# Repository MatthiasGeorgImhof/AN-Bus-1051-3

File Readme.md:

CAN transceiver from TX and RX to HIGH and LOW
Inspired by Adafruit but without buckconverter. Provide both 5 and 3.3V on pins

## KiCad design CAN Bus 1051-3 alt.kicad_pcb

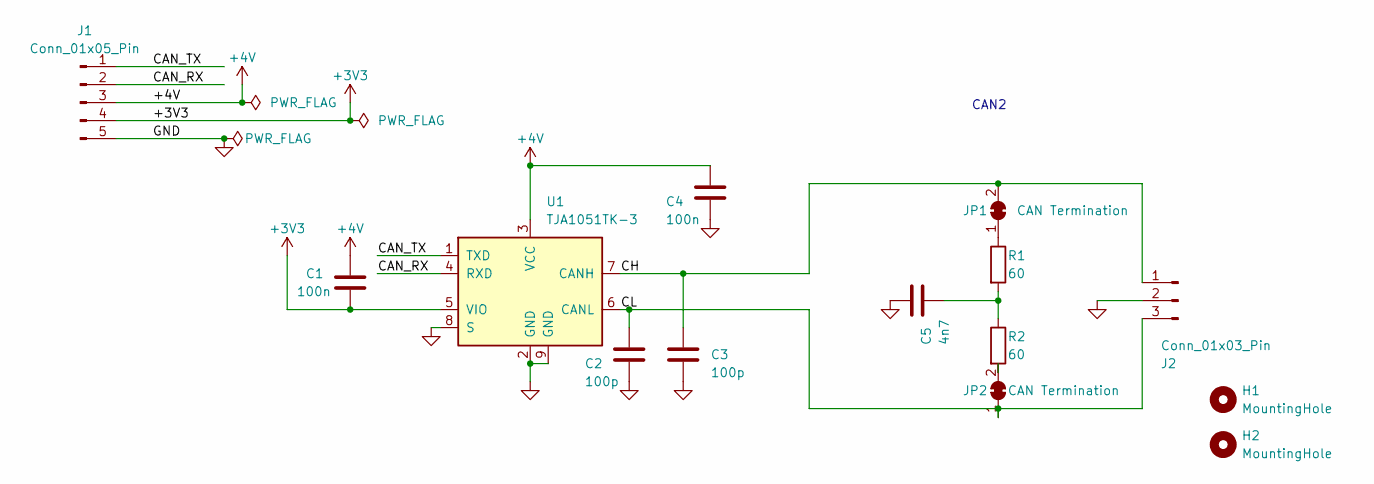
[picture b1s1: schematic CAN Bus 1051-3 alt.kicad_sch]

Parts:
C1, C4: 100n; C_0402_1005Metric; Voltage 16; Part Number CC0402KRX7R7BB104
C2, C3: 100p; C_0402_1005Metric; Voltage 16; Part Number CC0402KRX7R7BB101
C5: 4n7; C_0402_1005Metric; Voltage 16; Part Number CC0402KRX7R8BB472
H1, H2: MountingHole; MountingHole_2.2mm_M2
J1: Conn_01x05_Pin; PinHeader_1x05_P2.54mm_Vertical
J2: Conn_01x03_Pin; PinHeader_1x03_P2.54mm_Vertical
JP1, JP2: CAN Termination; SolderJumper-2_P1.3mm_Bridged_Pad1.0x1.5mm
R1, R2: 60; R_0402_1005Metric; Part Number RC0402FR-0760R4L
U1: TJA1051TK-3; DFN-8-1EP_3x3mm_P0.65mm_EP1.55x2.4mm; Part Number TJA1051TK/3,118

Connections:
+3V3: C1.2, J1.4, U1.5 (VIO)
+4V: C1.1, C4.1, J1.3, U1.3 (VCC)
/CAN_RX: J1.2, U1.4 (RXD)
/CAN_TX: J1.1, U1.1 (TXD)
/CH: C3.1, J2.1, JP1.2 (B), U1.7 (CANH)
/CL: C2.1, J2.3, JP2.1 (A), U1.6 (CANL)
GND: C2.2, C3.2, C4.2, C5.1, J1.5, J2.2, U1.2 (GND), U1.8 (S), U1.9 (GND)
unnamed: C5.2, R1.2, R2.1
unnamed: JP1.1 (A), R1.1
unnamed: JP2.2 (B), R2.2

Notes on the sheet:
CAN2

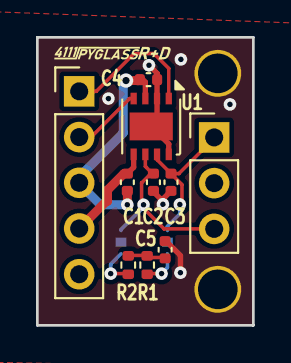
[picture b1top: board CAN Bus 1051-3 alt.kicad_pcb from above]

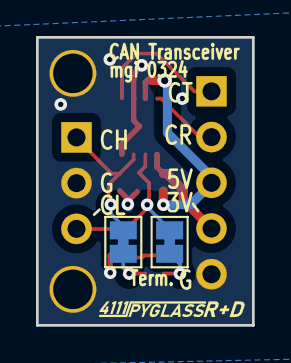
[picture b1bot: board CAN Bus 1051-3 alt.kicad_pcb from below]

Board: 2 copper layers, 12.0 x 16.0 mm, 14 parts (2 on the bottom side), 10 nets.

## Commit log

2024-07-22 init repo
2024-07-22 First layout
2024-07-22 alternate layout that conserves more space
